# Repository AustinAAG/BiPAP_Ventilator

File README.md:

# BiPAP Ventilator
 All code for BiPAP project

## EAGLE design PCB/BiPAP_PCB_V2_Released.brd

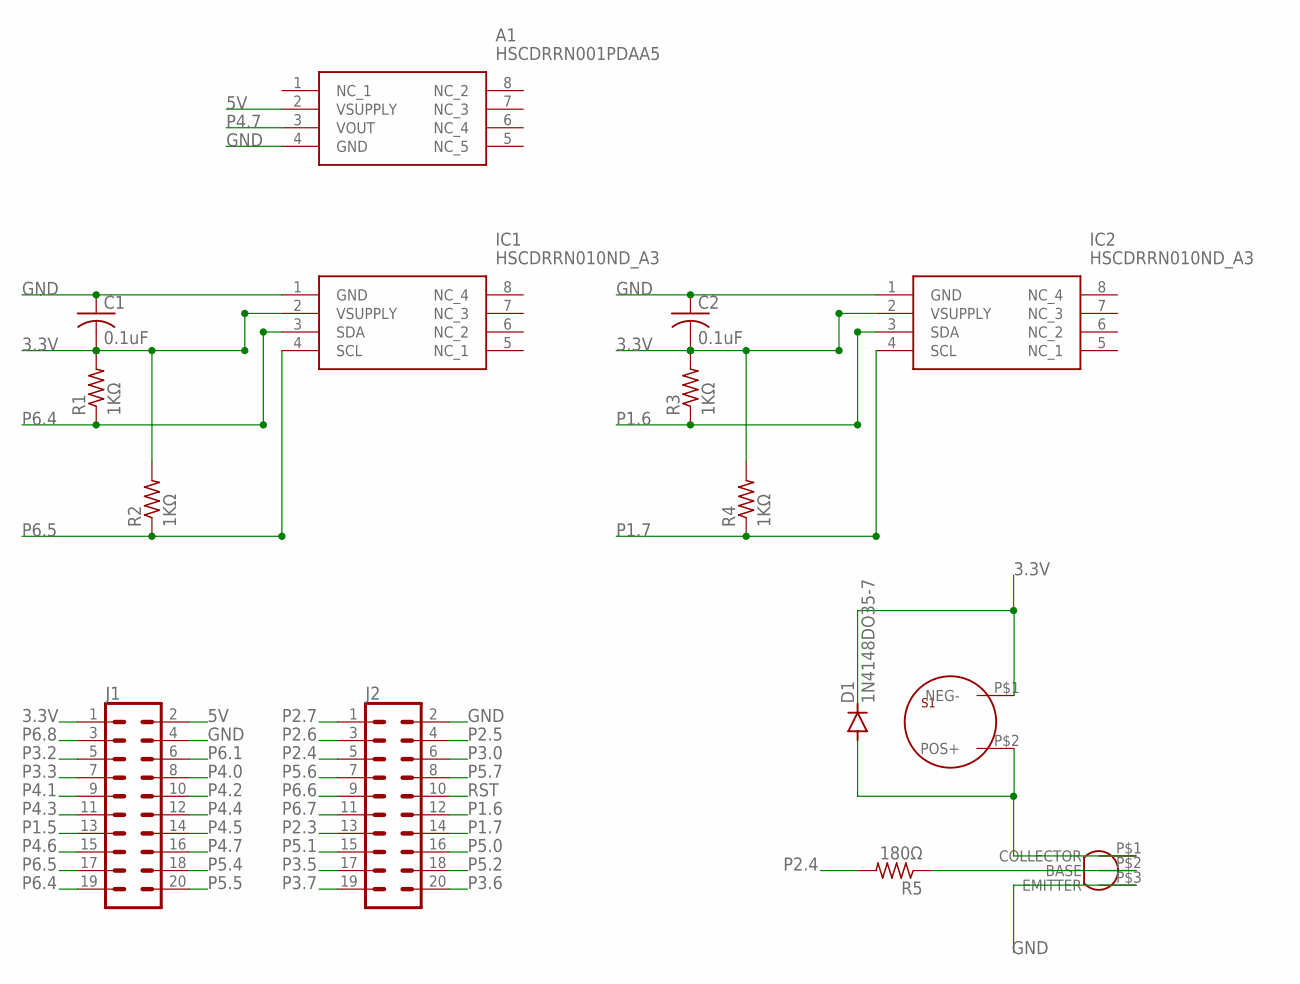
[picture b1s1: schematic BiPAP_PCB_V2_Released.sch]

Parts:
A1: HSCDRRN001PDAA5
C1, C2: 0.1uF; C0805
D1: 1N4148DO35-7; DO35-7
IC1, IC2: HSCDRRN010ND_A3; HSCDRRN010ND2A3
J1, J2: CONN_10X2; 2X10
R1, R2, R3, R4: 1KΩ; R0805
R5: 180Ω; R0805
S1: CEET120B085
T1: BC337

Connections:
3.3V: C1.2, C2.2, D1.C, IC1.2 (VSUPPLY), IC2.2 (VSUPPLY), J1.1, R1.2, R2.2, R3.2, R4.2, S1.P$1 (NEG-)
5V: A1.2 (VSUPPLY), J1.2
GND: A1.4 (GND), C1.1, C2.1, IC1.1 (GND), IC2.1 (GND), J1.4, J2.2, T1.P$3 (EMITTER)
unnamed: D1.A, S1.P$2 (POS+), T1.P$1 (COLLECTOR)
unnamed: R5.1, T1.P$2 (BASE)
P1.5: J1.13
P1.6: IC2.3 (SDA), J2.12, R3.1
P1.7: IC2.4 (SCL), J2.14, R4.1
P2.3: J2.13
P2.4: J2.5, R5.2
P2.5: J2.4
P2.6: J2.3
P2.7: J2.1
P3.0: J2.6
P3.2: J1.5
P3.3: J1.7
P3.5: J2.17
P3.6: J2.20
P3.7: J2.19
P4.0: J1.8
P4.1: J1.9
P4.2: J1.10
P4.3: J1.11
P4.4: J1.12
P4.5: J1.14
P4.6: J1.15
P4.7: A1.3 (VOUT), J1.16
P5.0: J2.16
P5.1: J2.15
P5.2: J2.18
P5.4: J1.18
P5.5: J1.20
P5.6: J2.7
P5.7: J2.8
P6.1: J1.6
P6.4: IC1.3 (SDA), J1.19, R1.1
P6.5: IC1.4 (SCL), J1.17, R2.1
P6.6: J2.9
P6.7: J2.11
P6.8: J1.3
RST: J2.10

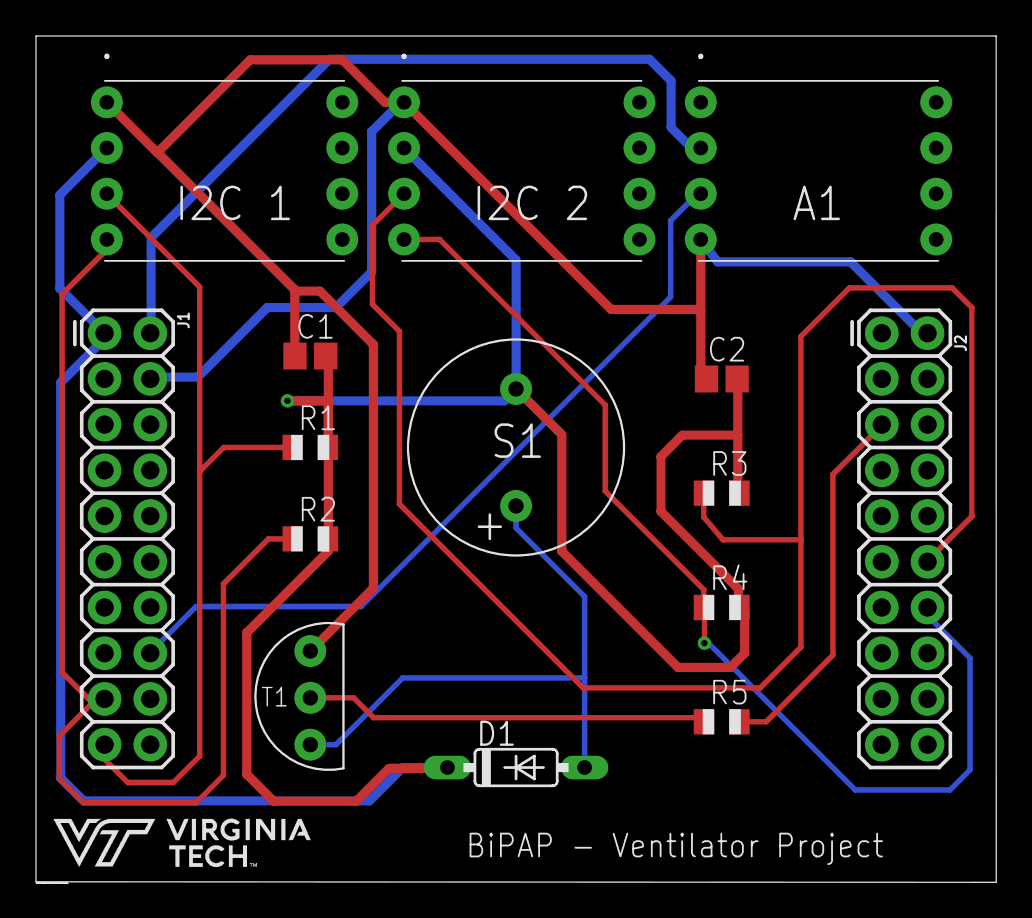
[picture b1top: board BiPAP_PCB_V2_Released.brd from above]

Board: 2 copper layers, 53.3 x 47.0 mm, 15 parts (0 on the bottom side), 11 nets.

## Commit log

2020-05-26 all files we use
    adding all the files we have generated so team has access
2020-05-29 files from demo on 5/28/2020
    Use these files for all working operations from the demo
2021-05-10 Inital commit
2021-05-10 intial commit of gui
2021-05-10 remove all old files
2021-05-10 Add read me file
2021-05-10 C code added
2021-05-10 Test from ccs
2021-05-10 test
2021-05-12 Deleted test file
2021-05-12 remove all unnecessary files
2021-05-12 Fixing Zero constants, Analog sensor, and prepping C code for pause button. Added more comments. Cleared unused code.
2021-05-12 fixed typos
2021-05-24 Fixed analog sensor and PWM conflicts
2021-05-24 Fixed comments
2021-05-24 Added Stop Button
2021-06-24 Added self calibration functionality
2021-07-05 added supp files
2021-07-09 Fixed self calibration problems
2021-07-12 meeting with dr meadows
2021-07-12 removed contstants to test callibration
2021-08-09 Revert "meeting with dr meadows"
    This reverts commit 2b0eddf21553a1879fe8fad9cf2999cda4b22817.
2021-08-09 corrected from misplaced commit

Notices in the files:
parts and their libraries:
SparkFun-Connectors: Licensing: Creative Commons ShareAlike 4.0 International - https://creativecommons.org/licenses/by-sa/4.0
